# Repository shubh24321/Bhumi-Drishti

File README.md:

# Bhumi Drishti 🛰️
### 1U CubeSat High-Altitude Balloon Mission

A student-built 1U CubeSat (100×100×113.5 mm) flown on a weather balloon
to the stratosphere. Sensors measure pressure, temperature, magnetic field,
and GPS coordinates throughout ascent and descent.

## Mission Overview

- **Platform:** 1U CubeSat form factor (100 × 100 × 113.5 mm)
- **Launch vehicle:** 600g weather balloon
- **Target altitude:** 20,000 – 40,000 m (stratosphere)
- **Flight computer:** Arduino Nano
- **Sensors:** BMP280 (pressure + temp) · HMC5883L (magnetometer) · Neo-6M (GPS)
- **Data storage:** SD card, CSV format
- **Recovery:** Parachute + GSM backup tracker

## Repository Structure
```
Bhumi-Drishti/
├── firmware/          # Arduino .ino source files
├── hardware/          # Wiring diagrams, PCB files
├── data/              # Sample CSV logs from tests
├── docs/              # Mission plan, test reports
└── analysis/          # Post-flight data scripts
```

## Current Status
- [x] Phase 1 — Team formed, workspace created
- [ ] Phase 2 — Sensor integration & demo build
- [ ] Phase 3 — Environmental testing
- [ ] Phase 4 — Launch preparation & DGCA approval
- [ ] Phase 5 — Launch & recovery

## Team
Built by a 4-person student team based in India.

## License
MIT — open science, open data.

## System Architecture
(docs/System Architecture/system architecture.png)

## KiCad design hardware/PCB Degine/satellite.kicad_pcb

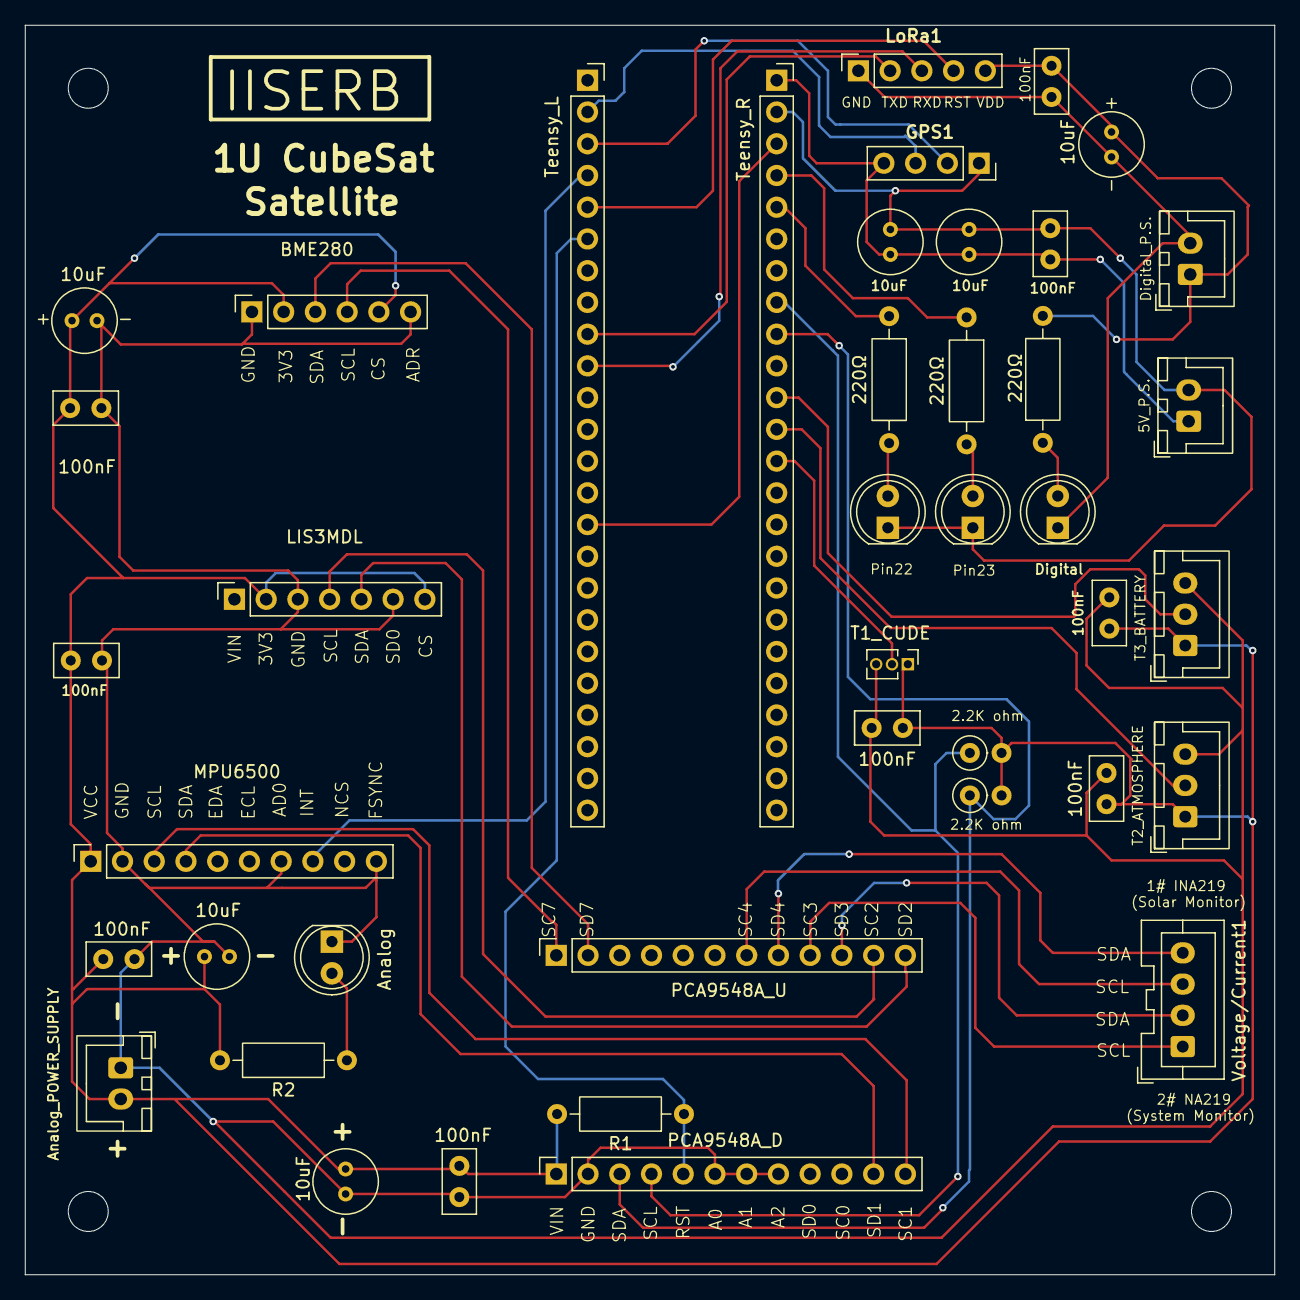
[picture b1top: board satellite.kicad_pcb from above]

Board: 2 copper layers, 100.0 x 100.0 mm, 46 parts (0 on the bottom side), 35 nets.

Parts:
5V_P.S.: Conn_01x02_Socket; JST_XH_B2B-XH-A_1x02_P2.50mm_Vertical
10uF, 10uF#2, 10uF#3, 10uF#4, 10uF#5, 10uF#6: C; C_Radial_D5.0mm_H5.0mm_P2.00mm
100nF, 100nF#2, 100nF#3, 100nF#4, 100nF#5, 100nF#6, 100nF#7, 100nF#8, 100nF#9: C; C_Disc_D5.0mm_W2.5mm_P2.50mm
Analog: LED; LED_D5.0mm
Analog_POWER_SUPPLY: Conn_01x02_Socket; JST_XH_B2B-XH-A_1x02_P2.50mm_Vertical
BME280: Conn_01x06_Socket; PinSocket_1x06_P2.54mm_Vertical
Digital: LED; LED_D5.0mm
Digital_P.S.: Conn_01x02_Socket; JST_XH_B2B-XH-A_1x02_P2.50mm_Vertical
GPS1: Conn_01x04_Socket; PinSocket_1x04_P2.54mm_Vertical
H1, H2, H3, H4: MountingHole; MountingHole_3.2mm_M3
LIS3MDL: Conn_01x07_Socket; PinSocket_1x07_P2.54mm_Vertical
LoRa1: Conn_01x05_Socket; PinSocket_1x05_P2.54mm_Vertical
MPU6500: Conn_01x10_Socket; PinSocket_1x10_P2.54mm_Vertical
PCA9548A_D, PCA9548A_U: Conn_01x12_Socket; PinSocket_1x12_P2.54mm_Vertical
Pin22, Pin23: LED; LED_D5.0mm
R1: 10kΩ; R_Axial_DIN0207_L6.3mm_D2.5mm_P10.16mm_Horizontal
R2, R3, R4, R5: 220Ω; R_Axial_DIN0207_L6.3mm_D2.5mm_P10.16mm_Horizontal
R6, R7: 2.2K; R_Axial_DIN0207_L6.3mm_D2.5mm_P2.54mm_Vertical
T1_CUDE: Conn_01x03_Socket; PinHeader_1x03_P1.27mm_Vertical
T2_ATMOSPHERE, T3_BATTERY: Conn_01x03_Socket; JST_XH_B3B-XH-A_1x03_P2.50mm_Vertical
Teensy_L: TEENSY 4.1; PinSocket_1x24_P2.54mm_Vertical
Teensy_R: Conn_01x24_Socket; PinSocket_1x24_P2.54mm_Vertical
Voltage/Current1: Conn_01x04_Pin; JST_XA_B04B-XASK-1_1x04_P2.50mm_Vertical

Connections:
/0: GPS1.3, Teensy_L.2
/1: GPS1.2, Teensy_L.3
/2: MPU6500.8, Teensy_L.4
/3: LoRa1.4, Teensy_L.5
/3.3V_A: 10uF#2.2, 10uF#3.2, 10uF#5.2, 100nF.2, 100nF#2.1, 100nF#3.2, 100nF#4.1, 100nF#6.2, 100nF#7.1, 100nF#9.1, Analog_POWER_SUPPLY.2, BME280.2, BME280.5, LIS3MDL.2, LIS3MDL.7, MPU6500.1, PCA9548A_D.1, R1.2, R2.2, R6.2, R7.2, T1_CUDE.1, T2_ATMOSPHERE.1, T3_BATTERY.1
/3.3V_T: Teensy_L.15, Teensy_R.3
/4: PCA9548A_D.5, R1.1, Teensy_L.6
/5V_Buck: 5V_P.S..1, 10uF.2, 10uF#6.2, 100nF#5.2, GPS1.4, Teensy_R.1
/7: LoRa1.2, Teensy_L.9
/8: LoRa1.3, Teensy_L.10
/14: T1_CUDE.2, Teensy_R.13
/15: T2_ATMOSPHERE.2, Teensy_R.12
/16: T3_BATTERY.2, Teensy_R.11
/18: PCA9548A_D.3, R7.1, Teensy_R.9
/19: PCA9548A_D.4, R6.1, Teensy_R.8
/22: R4.1, Teensy_R.5
/23: R5.1, Teensy_R.4
/A0: 10uF#2.1, 10uF#3.1, 10uF#5.1, 100nF.1, 100nF#2.2, 100nF#3.1, 100nF#4.2, 100nF#6.1, 100nF#7.2, 100nF#9.2, Analog.1 (K), Analog_POWER_SUPPLY.1, BME280.1, BME280.6, LIS3MDL.3, LIS3MDL.6, MPU6500.2, MPU6500.7, MPU6500.10, PCA9548A_D.2, PCA9548A_D.6, PCA9548A_D.7, PCA9548A_D.8, T1_CUDE.3, T2_ATMOSPHERE.3, T3_BATTERY.3
/GND_BUCK: 5V_P.S..2, 10uF.1, 10uF#6.1, 100nF#5.1, GPS1.1, Pin22.1 (K), Pin23.1 (K), Teensy_R.2
/GND_Digital: 10uF#4.1, 100nF#8.1, Digital.1 (K), Digital_P.S..2, LoRa1.1
/SC1: MPU6500.3, PCA9548A_D.12
/SC2: LIS3MDL.4, PCA9548A_U.11
/SC3: PCA9548A_U.9, Voltage/Current1.1
/SC4: PCA9548A_U.7, Voltage/Current1.3
/SC7: BME280.4, PCA9548A_U.1
/SD1: MPU6500.4, PCA9548A_D.11
/SD2: LIS3MDL.5, PCA9548A_U.12
/SD3: PCA9548A_U.10, Voltage/Current1.2
/SD4: PCA9548A_U.8, Voltage/Current1.4
/SD7: BME280.3, PCA9548A_U.2
/VCC_Digital: 10uF#4.2, 100nF#8.2, Digital_P.S..1, LoRa1.5, R3.2
unnamed: Analog.2 (A), R2.1
unnamed: Digital.2 (A), R3.1
unnamed: Pin22.2 (A), R4.2
unnamed: Pin23.2 (A), R5.2

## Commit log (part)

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2026-06-05 docs: add full mission README
2026-06-05 feat: add all sensor firmware files
2026-06-05 chore: remove untitled folder
2026-06-10 chore: create hardware folder
2026-06-10 docs: add system architecture diagram
2026-06-10 Add System Architecture section to README
